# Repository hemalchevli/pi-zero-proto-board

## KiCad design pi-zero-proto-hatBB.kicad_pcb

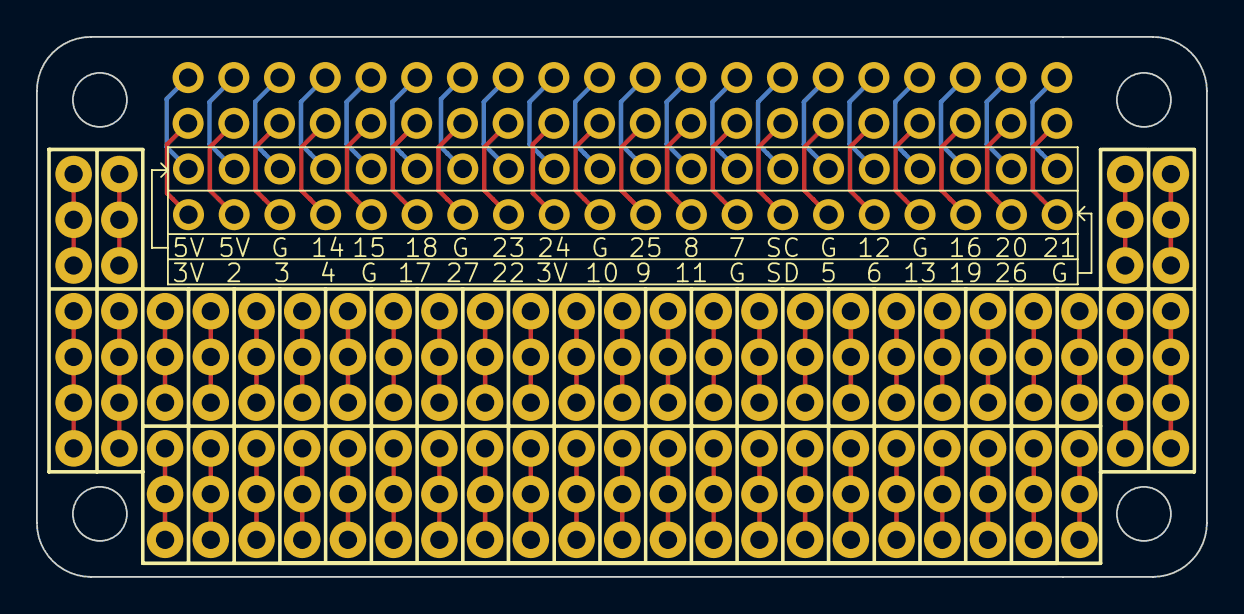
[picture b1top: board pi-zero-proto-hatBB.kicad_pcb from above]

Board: 2 copper layers, 65.0 x 30.0 mm, 52 parts (0 on the bottom side), 90 nets.

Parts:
P1, P2: CONN_02X20; Pin_Header_Straight_2x20_mod
P3, P4, P5, P6, P7, P8, P9, P10, P11, P12, P13, P14, P15, P16, P17, P18, P19, P20, P21, P22, P23, P24, P25, P26, P27, P28, P29, P30, P31, P32, P33, P34, P35, P36, P37, P38, P39, P40, P41, P42, P43, P44, P45, P46, P47, P48: CONN_01X03; Pin_Header_Straight_1x03_mod
P49, P50, P51, P52: CONN_01X04; Pin_Header_Straight_1x04_mod

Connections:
/2: P1.2, P2.2
/4: P1.4, P2.4
/6: P1.6, P2.6
/8: P1.8, P2.8
/10: P1.10, P2.10
/12: P1.12, P2.12
/14: P1.14, P2.14
/16: P1.16, P2.16
/18: P1.18, P2.18
/20: P1.20, P2.20
/22: P1.22, P2.22
/24: P1.24, P2.24
/26: P1.26, P2.26
/28: P1.28, P2.28
/30: P1.30, P2.30
/32: P1.32, P2.32
/34: P1.34, P2.34
/36: P1.36, P2.36
/38: P1.38, P2.38
/40: P1.40, P2.40
unnamed: P1.1, P2.1
unnamed: P1.3, P2.3
unnamed: P1.5, P2.5
unnamed: P1.7, P2.7
unnamed: P1.9, P2.9
unnamed: P1.11, P2.11
unnamed: P1.13, P2.13
unnamed: P1.15, P2.15
unnamed: P1.17, P2.17
unnamed: P1.19, P2.19
unnamed: P1.21, P2.21
unnamed: P1.23, P2.23
unnamed: P1.25, P2.25
unnamed: P1.27, P2.27
unnamed: P1.29, P2.29
unnamed: P1.31, P2.31
unnamed: P1.33, P2.33
unnamed: P1.35, P2.35
unnamed: P1.37, P2.37
unnamed: P1.39, P2.39
unnamed: P3.1, P3.2, P3.3
unnamed: P4.1, P4.2, P4.3
unnamed: P5.1, P5.2, P5.3
unnamed: P6.1, P6.2, P6.3
unnamed: P7.1, P7.2, P7.3
unnamed: P8.1, P8.2, P8.3
unnamed: P9.1, P9.2, P9.3
unnamed: P10.1, P10.2, P10.3
unnamed: P11.1, P11.2, P11.3
unnamed: P12.1, P12.2, P12.3
unnamed: P13.1, P13.2, P13.3
unnamed: P14.1, P14.2, P14.3
unnamed: P15.1, P15.2, P15.3
unnamed: P16.1, P16.2, P16.3
unnamed: P17.1, P17.2, P17.3
unnamed: P18.1, P18.2, P18.3
unnamed: P19.1, P19.2, P19.3
unnamed: P20.1, P20.2, P20.3
unnamed: P21.1, P21.2, P21.3
unnamed: P22.1, P22.2, P22.3
unnamed: P23.1, P23.2, P23.3
unnamed: P24.1, P24.2, P24.3
unnamed: P25.1, P25.2, P25.3
unnamed: P26.1, P26.2, P26.3
unnamed: P27.1, P27.2, P27.3
unnamed: P28.1, P28.2, P28.3
unnamed: P29.1, P29.2, P29.3
unnamed: P30.1, P30.2, P30.3
unnamed: P31.1, P31.2, P31.3
unnamed: P32.1, P32.2, P32.3
unnamed: P33.1, P33.2, P33.3
unnamed: P34.1, P34.2, P34.3
unnamed: P35.1, P35.2, P35.3
unnamed: P36.1, P36.2, P36.3
unnamed: P37.1, P37.2, P37.3
unnamed: P38.1, P38.2, P38.3
unnamed: P39.1, P39.2, P39.3
unnamed: P40.1, P40.2, P40.3
unnamed: P41.1, P41.2, P41.3
unnamed: P42.1, P42.2, P42.3
unnamed: P43.1, P43.2, P43.3
unnamed: P44.1, P44.2, P44.3
unnamed: P45.1, P45.2, P45.3
unnamed: P46.1, P46.2, P46.3
unnamed: P47.1, P47.2, P47.3
unnamed: P48.1, P48.2, P48.3
unnamed: P49.1, P49.2, P49.3, P49.4
unnamed: P50.1, P50.2, P50.3, P50.4
unnamed: P51.1, P51.2, P51.3, P51.4
unnamed: P52.1, P52.2, P52.3, P52.4
